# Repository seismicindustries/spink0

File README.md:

# spink0

This repository contains the source code and the schematics for an Ableton Link to clock/reset converter.

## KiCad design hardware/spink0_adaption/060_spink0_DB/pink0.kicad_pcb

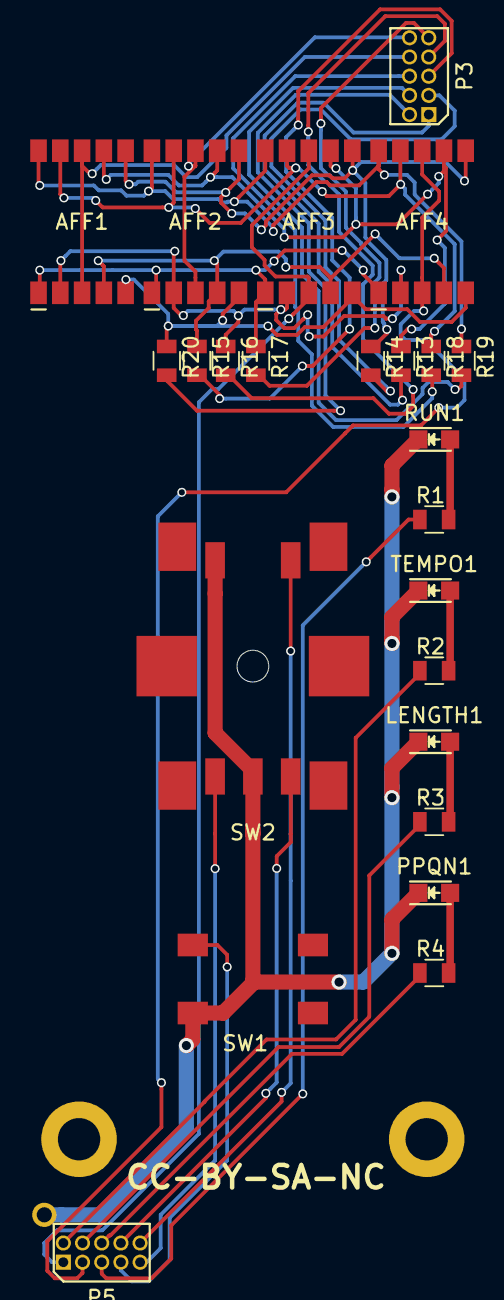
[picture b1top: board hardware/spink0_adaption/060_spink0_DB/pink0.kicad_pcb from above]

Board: 2 copper layers, 24 parts (0 on the bottom side), 33 nets.

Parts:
AFF1, AFF2, AFF3, AFF4: 7SEGMENTS; ACSA02_KCSA02_7segment
LENGTH1: LED; LED_0805
P3, P5: CONN_02X05; PINHEAD_10_pin_jtag_connector
PPQN1: LED; LED_0805
R1, R2, R3, R4, R13, R14, R15, R16, R17, R18, R19, R20: R; R_0805
RUN1: LED; LED_0805
SW1: SW_PUSH_SMALL_H; APEM_tactile_SMD_switch_6mm
SW2: Rotary_Encoder_Switch; ENCODER_PEC11_SMD
TEMPO1: LED; LED_0805

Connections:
A: AFF1.7, AFF2.7, AFF3.7, AFF4.7, R13.1
B: AFF1.6, AFF2.6, AFF3.6, AFF4.6, R14.1
C: AFF1.4, AFF2.4, AFF3.4, AFF4.4, R15.1
D: AFF1.2, AFF2.2, AFF3.2, AFF4.2, R16.1
DP: AFF1.5, AFF2.5, AFF3.5, AFF4.5, R20.1
E: AFF1.1, AFF2.1, AFF3.1, AFF4.1, R17.1
Earth: LENGTH1.1, PPQN1.1, RUN1.1, SW1.2, SW2.2, SW2.5, TEMPO1.1
F: AFF1.9, AFF2.9, AFF3.9, AFF4.9, R18.1
G: AFF1.10, AFF2.10, AFF3.10, AFF4.10, R19.1
GPIO2: P5.6, R4.1
GPIO3: P5.4, R3.1
GPIO4: P3.4, R19.2
GPIO5: P5.7, SW1.1
GPIO6: P5.10, SW2.4
GPIO7: P5.5, R1.1
GPIO8: P3.1, R13.2
GPIO9: P3.9, R17.2
GPIO10: P3.5, R15.2
GPIO11: AFF1.3, AFF1.8, P3.8
GPIO15: AFF4.3, AFF4.8, P5.3
GPIO16: P5.8, SW2.3
GPIO17: P3.7, R16.2
GPIO19: P5.9, SW2.1
GPIO22: AFF3.3, AFF3.8, P5.1
GPIO23: P3.6, R18.2
GPIO24: AFF2.3, AFF2.8, P3.10
GPIO25: P3.3, R14.2
GPIO27: P3.2, R20.2
unnamed: LENGTH1.2, R3.2
unnamed: PPQN1.2, R4.2
unnamed: R1.2, RUN1.2
unnamed: R2.2, TEMPO1.2
T_LED: P5.2, R2.1

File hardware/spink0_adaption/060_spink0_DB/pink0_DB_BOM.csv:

Refs,Value,Footprint,QTY,MFR,MPN,SPR,SPN
RUN1;TEMPO1;LENGTH1;PPQN1,LED,LEDs:LED_0805,4,Avago / Broadcom,HSMH-C170,Mouser,630-HSMH-C170
AFF1;AFF2;AFF3;AFF4,7SEGMENTS,raffilibkicad:ACSA02_KCSA02_7segment,4,Kingbright,ACSA02-41YWA-F01,Mouser,604-ACSA02-41YWA
SW1,SW_PUSH_SMALL_H,raffilibkicad:APEM_tactile_SMD_switch_6mm,1,APEM,ADTSM66NV,Mouser,642-ADTSM66NV
SW2,Rotary_Encoder_Switch,raffilibkicad:ENCODER_PEC11_SMD,1,Bourns,PEC11S-929K-S0015,Mouser,652-PEC11S9215KH0015
P3;P5,CONN_02X05,raffilibkicad:PINHEAD_10_pin_jtag_connector,2,Amphenol FCI,20021111-00010T4LF,Mouser,649-221111-00010T4LF
R1;R2;R3;R4;R13;R14;R15;R16;R17;R18;R19;R20,100,raffilibkicad:R_0805,12,Yageo,RC0805FR-07100RL,Mouser,603-RC0805FR-07100RL

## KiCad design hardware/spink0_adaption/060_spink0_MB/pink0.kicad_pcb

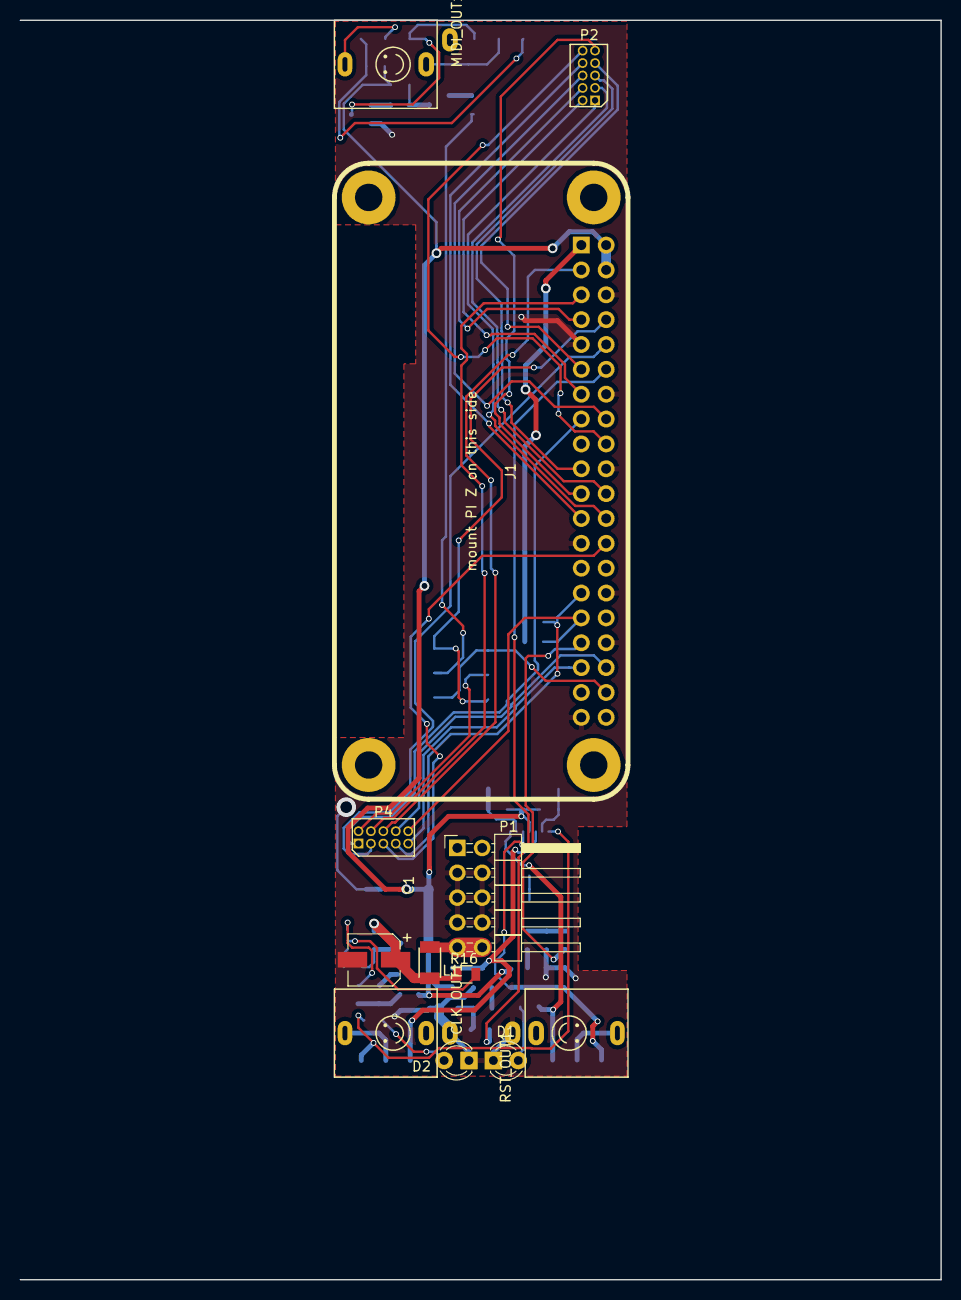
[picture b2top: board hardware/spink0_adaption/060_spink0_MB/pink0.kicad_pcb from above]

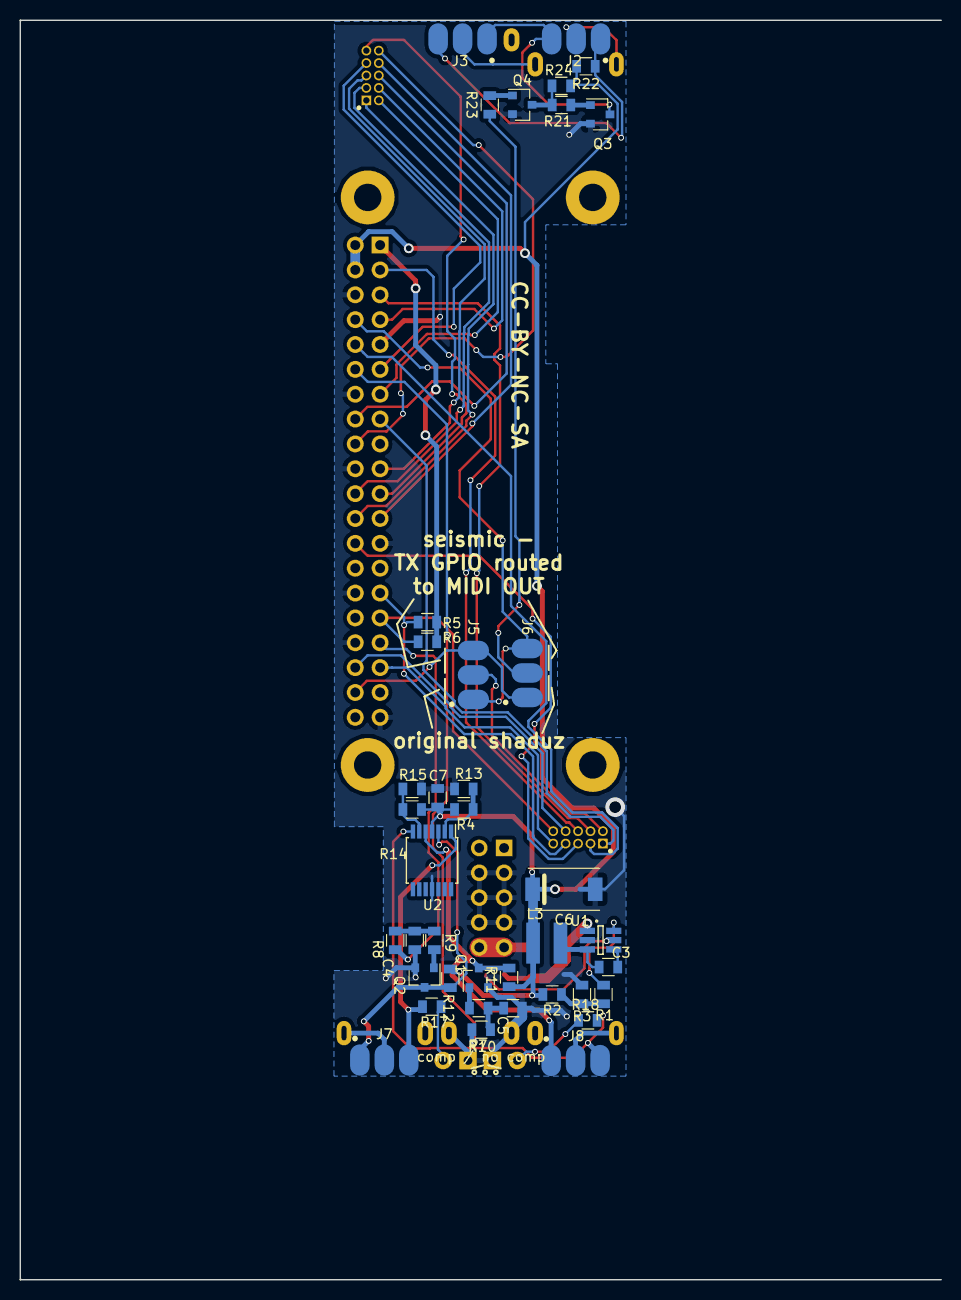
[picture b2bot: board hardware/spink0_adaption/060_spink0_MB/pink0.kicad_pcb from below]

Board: 2 copper layers, 94.1 x 128.7 mm, 51 parts (39 on the bottom side), 56 nets.

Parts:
C1: 22u; CP_Elec_5x5.3
C3: 1u; C_0805
C4, C5: 33n; C_0805
C6: 22u; CP_Elec_7.3x4.3
C7: 100n; C_0805
CLK_OUT1: JACK_QINGPU; jack_qingpu
D1, D2: LED; LED_D3.0mm
J1: PI_ZERO
J2, J3, J5, J6, J7, J8: GS3; solderbridge
L1: INDUCTOR; Inductor_PSU_NLCV32T
L3: 6.8uH; Inductor_SRN4018TA_bourns
MIDI_OUT1: JACK_QINGPU; jack_qingpu
P1: CONN_02X05; Pin_Header_Angled_2x05_Pitch2.54mm_with_space_for_con
P2, P4: CONN_02X05; PINHEAD_10_pin_jtag_connector
Q1, Q2, Q3, Q4: BC849; SOT-23
R1: 75k; R_0805
R2: 40k2; R_0805
R3: 7k68; R_0805
R4, R7, R8, R9, R10, R11, R12, R13, R14, R15, R17, R18: 1k; R_0805
R5, R6, R21, R23, R24: 10k; R_0805
R16: 100k; R_0805
R22: 220; R_0805
RST_OUT1: JACK_QINGPU; jack_qingpu
U1: MP1469; SOT-23-6
U2: MCP6004; TSSOP-14_4.4x5mm_Pitch0.65mm

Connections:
+3V3: J1.1, R5.1, R6.1
+5V: C6.1, C7.2, J1.2, J1.4, L3.1, R2.2, R4.1, R11.2, R12.2, R14.1, R22.1, R24.2, U2.4
+12VA: C1.1, L1.1, R16.1, U1.1
CLK_OUT: J8.1, Q1.3, R11.1, U2.5
Earth: C1.2, C4.2, C5.2, C6.2, C7.1, CLK_OUT1.1, D1.1, D2.1, J1.6, J1.9, J1.14, J1.20, J1.25, J1.30, J1.34, J1.39, P1.3, P1.4, P1.5, P1.6, P1.7, P1.8, Q1.2, Q2.2, Q3.2, Q4.2, R3.1, R13.2, R15.2, RST_OUT1.1, U1.2, U2.11
GPIO2: J1.3, P4.6
GPIO3: J1.5, P4.4
GPIO4: J1.7, P2.4
GPIO5: J1.29, P4.7, R5.2
GPIO6: J1.31, P4.10, R6.2
GPIO7: J1.26, P4.5
GPIO8: J1.24, P2.1
GPIO9: J1.21, P2.9
GPIO10: J1.19, P2.5
GPIO11: J1.23, P2.8
GPIO14: J1.8, J5.1, J6.3
GPIO15: J1.10, P4.3
GPIO16: J1.36, P4.8
GPIO17: J1.11, P2.7
GPIO19: J1.35, P4.9
GPIO20: J1.38, J5.3, J6.1
GPIO22: J1.15, P4.1
GPIO23: J1.16, P2.6
GPIO24: J1.18, P2.10
GPIO25: J1.22, P2.3
GPIO27: J1.13, P2.2
unnamed: C3.1, L3.2, U1.3
unnamed: C3.2, U1.4
unnamed: C4.1, R8.1, R9.2
unnamed: C5.1, R7.1, R10.2
unnamed: CLK_OUT1.3, J8.2
unnamed: D1.2, R17.1
unnamed: D2.2, R18.1
unnamed: J2.1, J3.3, R22.2
unnamed: J2.2, MIDI_OUT1.3
unnamed: J2.3, J3.1, Q3.3
unnamed: J3.2, MIDI_OUT1.2
unnamed: J6.2, R23.2
unnamed: J7.2, RST_OUT1.3
unnamed: J7.3, R17.2, U2.1
unnamed: J8.3, R18.2, U2.7
unnamed: L1.2, P1.9, P1.10
unnamed: Q1.1, R10.1
unnamed: Q2.1, R9.1
unnamed: Q3.1, R21.1
unnamed: Q4.1, R23.1
unnamed: Q4.3, R21.2, R24.1
unnamed: R1.1, U1.6
unnamed: R1.2, R2.1, R3.2
unnamed: R4.2, R13.1, U2.2
unnamed: R14.2, R15.1, U2.6
unnamed: R16.2, U1.5
PWMA_L: J1.12, R7.2
PWMA_R: J1.33, R8.2
RST_OUT: J7.1, Q2.3, R12.1, U2.3
T_LED: J5.2, P4.2

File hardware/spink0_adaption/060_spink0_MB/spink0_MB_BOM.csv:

Refs,Value,Footprint,QTY,MFR,MPN,SPR,SPN
C1,22u,raffilibkicad:CP_Elec_5x5.3,1,Panasonic,EEE-FK1C220R,Mouser,667-EEE-FK1C220R
C6,22u,raffilibkicad:CP_Elec_7.3x4.3,1,Panasonic,EEF-HX1D220R,Mouser,667-EEF-HX1D220R
C7,100n,raffilibkicad:C_0805,1,AVX,08055C104KAT2A,Mouser,581-08055C104K
C3,1u,raffilibkicad:C_0805,1,Taiyo Yuden,UMK212B7105KG-T,Mouser,963-UMK212B7105KG-T
C4;C5,33n,raffilibkicad:C_0805,2,Kemet,C0805C333K5RACTU,Mouser,80-C0805C333K5R
L1,INDUCTOR,raffilibkicad:Inductor_PSU_NLCV32T,1,TDK,NLCV32T-R10M-PFR,Mouser,810-NLCV32T-R10M-PFR
L3,6.8uH,raffilibkicad:Inductor_SRN4018TA_bourns,1,Bourns,SRN4018TA-6R8M,Mouser,652-SRN4018TA-6R8M
D2;D1,LED,raffilibkicad:LED_D3.0mm,2,Lite-On,LTL-4231N,Mouser,859-LTL-4231N
P2;P4,CONN_02X05,raffilibkicad:PINHEAD_10_pin_jtag_connector,2,Amphenol FCI,20021111-00010T4LF,Mouser,649-221111-00010T4LF
J1,PI_ZERO,raffilibkicad:PI_ZERO,1,,,your PI supplier,
P1,CONN_02X05,raffilibkicad:Pin_Header_Angled_2x05_Pitch2.54mm_with_space_for_con,1,Amphenol FCI,649-68020-110HLF,Mouser,68020-110HLF
R16,100k,raffilibkicad:R_0805,1,Yageo,RC0805FR-07100KL,Mouser,603-RC0805FR-07100KL
R5;R6;R21;R24;R23,10k,raffilibkicad:R_0805,5,Vishay,CRCW080510K0FKEAC,Mouser,71-CRCW080510K0FKEAC
R10;R7;R9;R8;R12;R11;R13;R4;R14;R15;R17;R18,1k,raffilibkicad:R_0805,12,Vishay,CRCW08051K00FKEAC,Mouser,71-CRCW08051K00FKEAC
R22,220,raffilibkicad:R_0805,1,Bourns,CR0805-FX-2200GLF,Mouser,652-CR0805-FX2200GLF
R2,40k2,raffilibkicad:R_0805,1,Yageo,RC0805FR-0740K2L,Mouser,603-RC0805FR-0740K2L
R1,75k,raffilibkicad:R_0805,1,Vishay,CRCW080575K0FKEA,Mouser,71-CRCW0805-75K-E3
R3,7k68,raffilibkicad:R_0805,1,Yageo,RC0805FR-077K68L,Mouser,603-RC0805FR-077K68L
Q1;Q2;Q3;Q4,BC849,raffilibkicad:SOT-23,4,,,Mouser,771-BC849C-T/R
U1,MP1469,raffilibkicad:SOT-23-6,1,MPS,MP1469GJ-Z,Mouser,946-MP1469GJZ
U2,MCP6004,raffilibkicad:TSSOP-14_4.4x5mm_Pitch0.65mm,1,Microchip Techology,MCP6004-I/ST,Mouser,579-MCP6004-I/ST
CLK_OUT1;RST_OUT1;MIDI_OUT1,JACK_QINGPU,raffilibkicad:jack_qingpu,3,,,,
J6;J5;J8;J7,GS3,raffilibkicad:solderbridge,4,,,,

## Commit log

2018-02-12 readme modified
2018-02-13 new raspap source
2018-02-13 moved addnet and css to support folder, changed hostapd creds
2018-02-20 moved mode switching script to support folder, src_raffi deleted, mode switch scipt added to crontab via installscript
2018-02-20 Hardware Sourcefiles added, fresh gerber MK1 merge added
2018-02-20 add copy of HW files
2018-02-20 HW file upload, 2nd try..
2018-02-20 wrong BCM in comment 20 -> 28
2018-03-16 fresh build on rt_preempt OS - changed wlan-mode script execution from cron to systemd
2018-03-16 added cat
2018-03-16 del pishrink
2018-03-16 fixed some typos - build ok

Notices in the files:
hardware/spink0_adaption/060_spink0_DB/pink0.kicad_pcb:
CC-BY-SA-NC
hardware/spink0_adaption/060_spink0_MB/pink0.kicad_pcb:
CC-BY-NC-SA
